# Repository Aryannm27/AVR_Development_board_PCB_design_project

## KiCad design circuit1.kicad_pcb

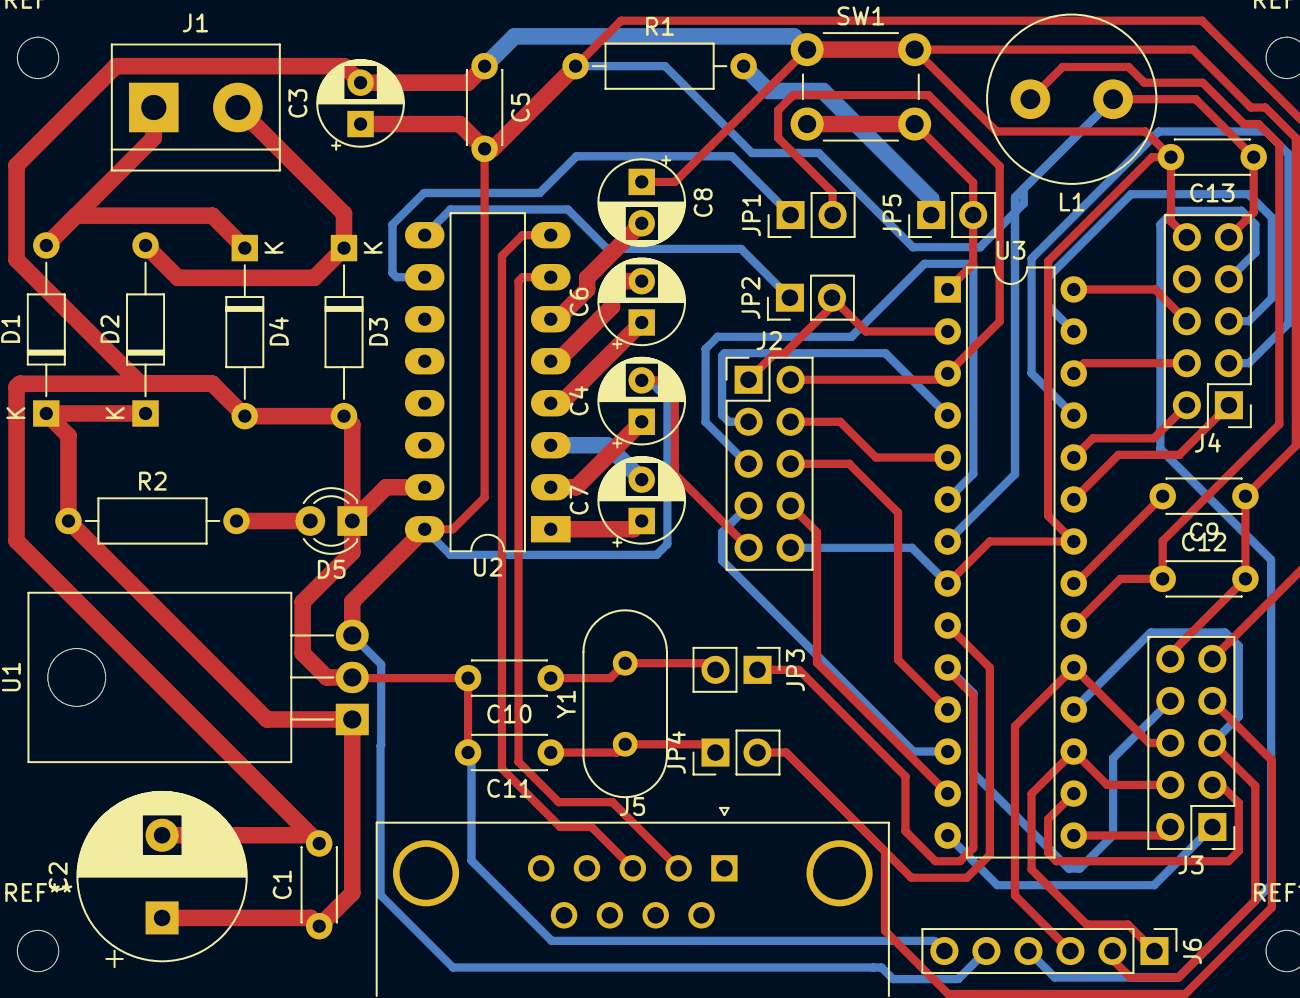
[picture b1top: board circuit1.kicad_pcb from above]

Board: 2 copper layers, 37 parts (0 on the bottom side), 45 nets.

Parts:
C1, C5, C9, C12, C13: 0.1uF; C_Disc_D4.3mm_W1.9mm_P5.00mm
C2: 1000uf/25V; CP_Radial_D10.0mm_P5.00mm
C3: 100uF; CP_Radial_D5.0mm_P2.50mm
C4, C6, C7, C8: 10uF; CP_Radial_D5.0mm_P2.50mm
C10, C11: 33pF; C_Disc_D4.3mm_W1.9mm_P5.00mm
D1, D2, D3, D4: 1N4007; D_DO-35_SOD27_P10.16mm_Horizontal
D5: LED; LED_D3.0mm
J1: Screw_Terminal_01x02; TerminalBlock_bornier-2_P5.08mm
J2, J3, J4: Conn_02x05_Odd_Even; PinHeader_2x05_P2.54mm_Vertical
J5: DB9_Female; DSUB-9_Female_Horizontal_P2.77x2.84mm_EdgePinOffset4.94mm_H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
J6: Conn_01x06_Female; PinHeader_1x06_P2.54mm_Vertical
JP1, JP2, JP3, JP4, JP5: Jumper; PinHeader_1x02_P2.54mm_Vertical
L1: 100uH; L_Radial_D10.0mm_P5.00mm_Neosid_SD12k_style3
R1: 100K; R_Axial_DIN0207_L6.3mm_D2.5mm_P10.16mm_Horizontal
R2: 1K; R_Axial_DIN0207_L6.3mm_D2.5mm_P10.16mm_Horizontal
SW1: REST; SW_PUSH_6mm
U1: L7805; TO-220-3_Horizontal_TabDown
U2: MAX232; DIP-16_W7.62mm_LongPads
U3: ATmega8L-8PU; DIP-28_W7.62mm
Y1: Crystal; Crystal_HC18-U_Vertical

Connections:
5V: C3.1, C4.2, C5.2, C13.1, J2.9, J3.9, J4.9, J6.5, L1.1, R1.1, U1.3, U2.16, U3.7
GND: C1.2, C2.2, C3.2, C5.1, C8.1, C9.1, C10.2, C11.2, C12.2, C13.2, D3.2, D4.2, D5.1, J2.10, J3.10, J4.10, J6.6, SW1.1, U1.2, U2.15, U3.8, U3.22
unnamed: C1.1, C2.1, D1.1, D2.1, R2.1, U1.1
unnamed: C4.1, U2.2
unnamed: C6.1, U2.4
unnamed: C6.2, U2.5
unnamed: C7.1, U2.1
unnamed: C7.2, U2.3
unnamed: C8.2, U2.6
unnamed: C9.2, U3.21
unnamed: C10.1, JP3.2, Y1.2
unnamed: C11.1, JP4.1, Y1.1
unnamed: C12.1, L1.2, U3.20
unnamed: D1.2, D4.1, J1.1
unnamed: D2.2, D3.1, J1.2
unnamed: D5.2, R2.2
unnamed: J5.2, U2.7
unnamed: J5.3, U2.8
unnamed: JP1.1, U2.10
unnamed: JP2.1, U2.9
unnamed: JP5.1, R1.2
unnamed: JP5.2, SW1.2, U3.1
PB0: J3.1, U3.14
PB1: J3.2, U3.15
PB2: J3.3, U3.16
PB3: J3.4, J6.1, U3.17
PB4: J3.5, J6.2, U3.18
PB5: J3.6, J6.3, U3.19
PB6: J3.7, JP4.2, U3.9
PB7: J3.8, JP3.1, U3.10
PC0: J4.1, U3.23
PC1: J4.2, U3.24
PC2: J4.3, U3.25
PC3: J4.4, U3.26
PC4: J4.5, U3.27
PC5: J4.6, U3.28
PC6: J4.7, J6.4
PD0: J2.1, JP2.2, U3.2
PD1: J2.2, JP1.2, U3.3
PD2: J2.3, U3.4
PD3: J2.4, U3.5
PD4: J2.5, U3.6
PD5: J2.6, U3.11
PD6: J2.7, U3.12
PD7: J2.8, U3.13

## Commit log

2023-12-19 the required file
